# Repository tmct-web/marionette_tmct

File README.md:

# marionette_tmct

## What is "Marionette" ?
Marionettes are so-called puppets.We created this to remotely control multiple remote devices via USB from a single PC.

This system contains two Arduino Leonardo, the controlling side (master side) and the controlled side (slave side).

For example, the USB port connected to the controlling side (master side) is USB-COM, and the USB port connected to the controlled side (slave side) is an HID keyboard (= the slave side looks like a normal HID keyboard). Then you can control the slave keyboard with USB-COM on the master.

マリオネッテと書いてマリオネットと読みます。マリオネットはいわゆる操り人形のことですね。
もともと1台のパソコンからUSB経由で複数の相手機器を遠隔コントロールするために作ったものです。

このシステムは、制御する側（マスタ側）・制御される側（スレーブ側）の2つ分のArduino Leonardoが入っている、ちょっと変わったハードウェアになっています。

たとえば制御する側（マスタ側）に繋がるUSBポートはUSB-COM、制御される側（スレーブ側）につながるUSBポートはHIDキーボード（＝スレーブ側は普通のHIDキーボードに見える）、という構成にすると、マスタ側のUSB-COMでスレーブ側をキーボード制御する、なんてことができます。

## Hardware specifications
Marionette has two circuits of Arduino Leonardo.

The two circuits are called a master (MASTER) and a slave (SLAVE), respectively, and can be operated completely differently by different programs. The hardware block diagram is shown below.

MarionetteはArduino Leonardoの2枚分の回路が実装されています。

2枚分の回路はそれぞれマスタ(MASTER)とスレーブ(SLAVE)と呼び、各々別のプログラムでまったく別の動作をさせることができます。ハードウェアのブロック図を以下に示します。

See our [homepage](https://ss1.xrea.com/tmct.s1009.xrea.com/work/td-ja-7e2g01.html) for more information.(* Japanese only)

詳細は [ホームページ](https://ss1.xrea.com/tmct.s1009.xrea.com/work/td-ja-7e2g01.html) を参照してください。

## Recommended projects
We recommend this project. Compatibility with Marionette is outstanding.

Marionetteで使用すると、良い結果が得られるでしょう。

[NicoHood/HID](https://github.com/NicoHood/HID)

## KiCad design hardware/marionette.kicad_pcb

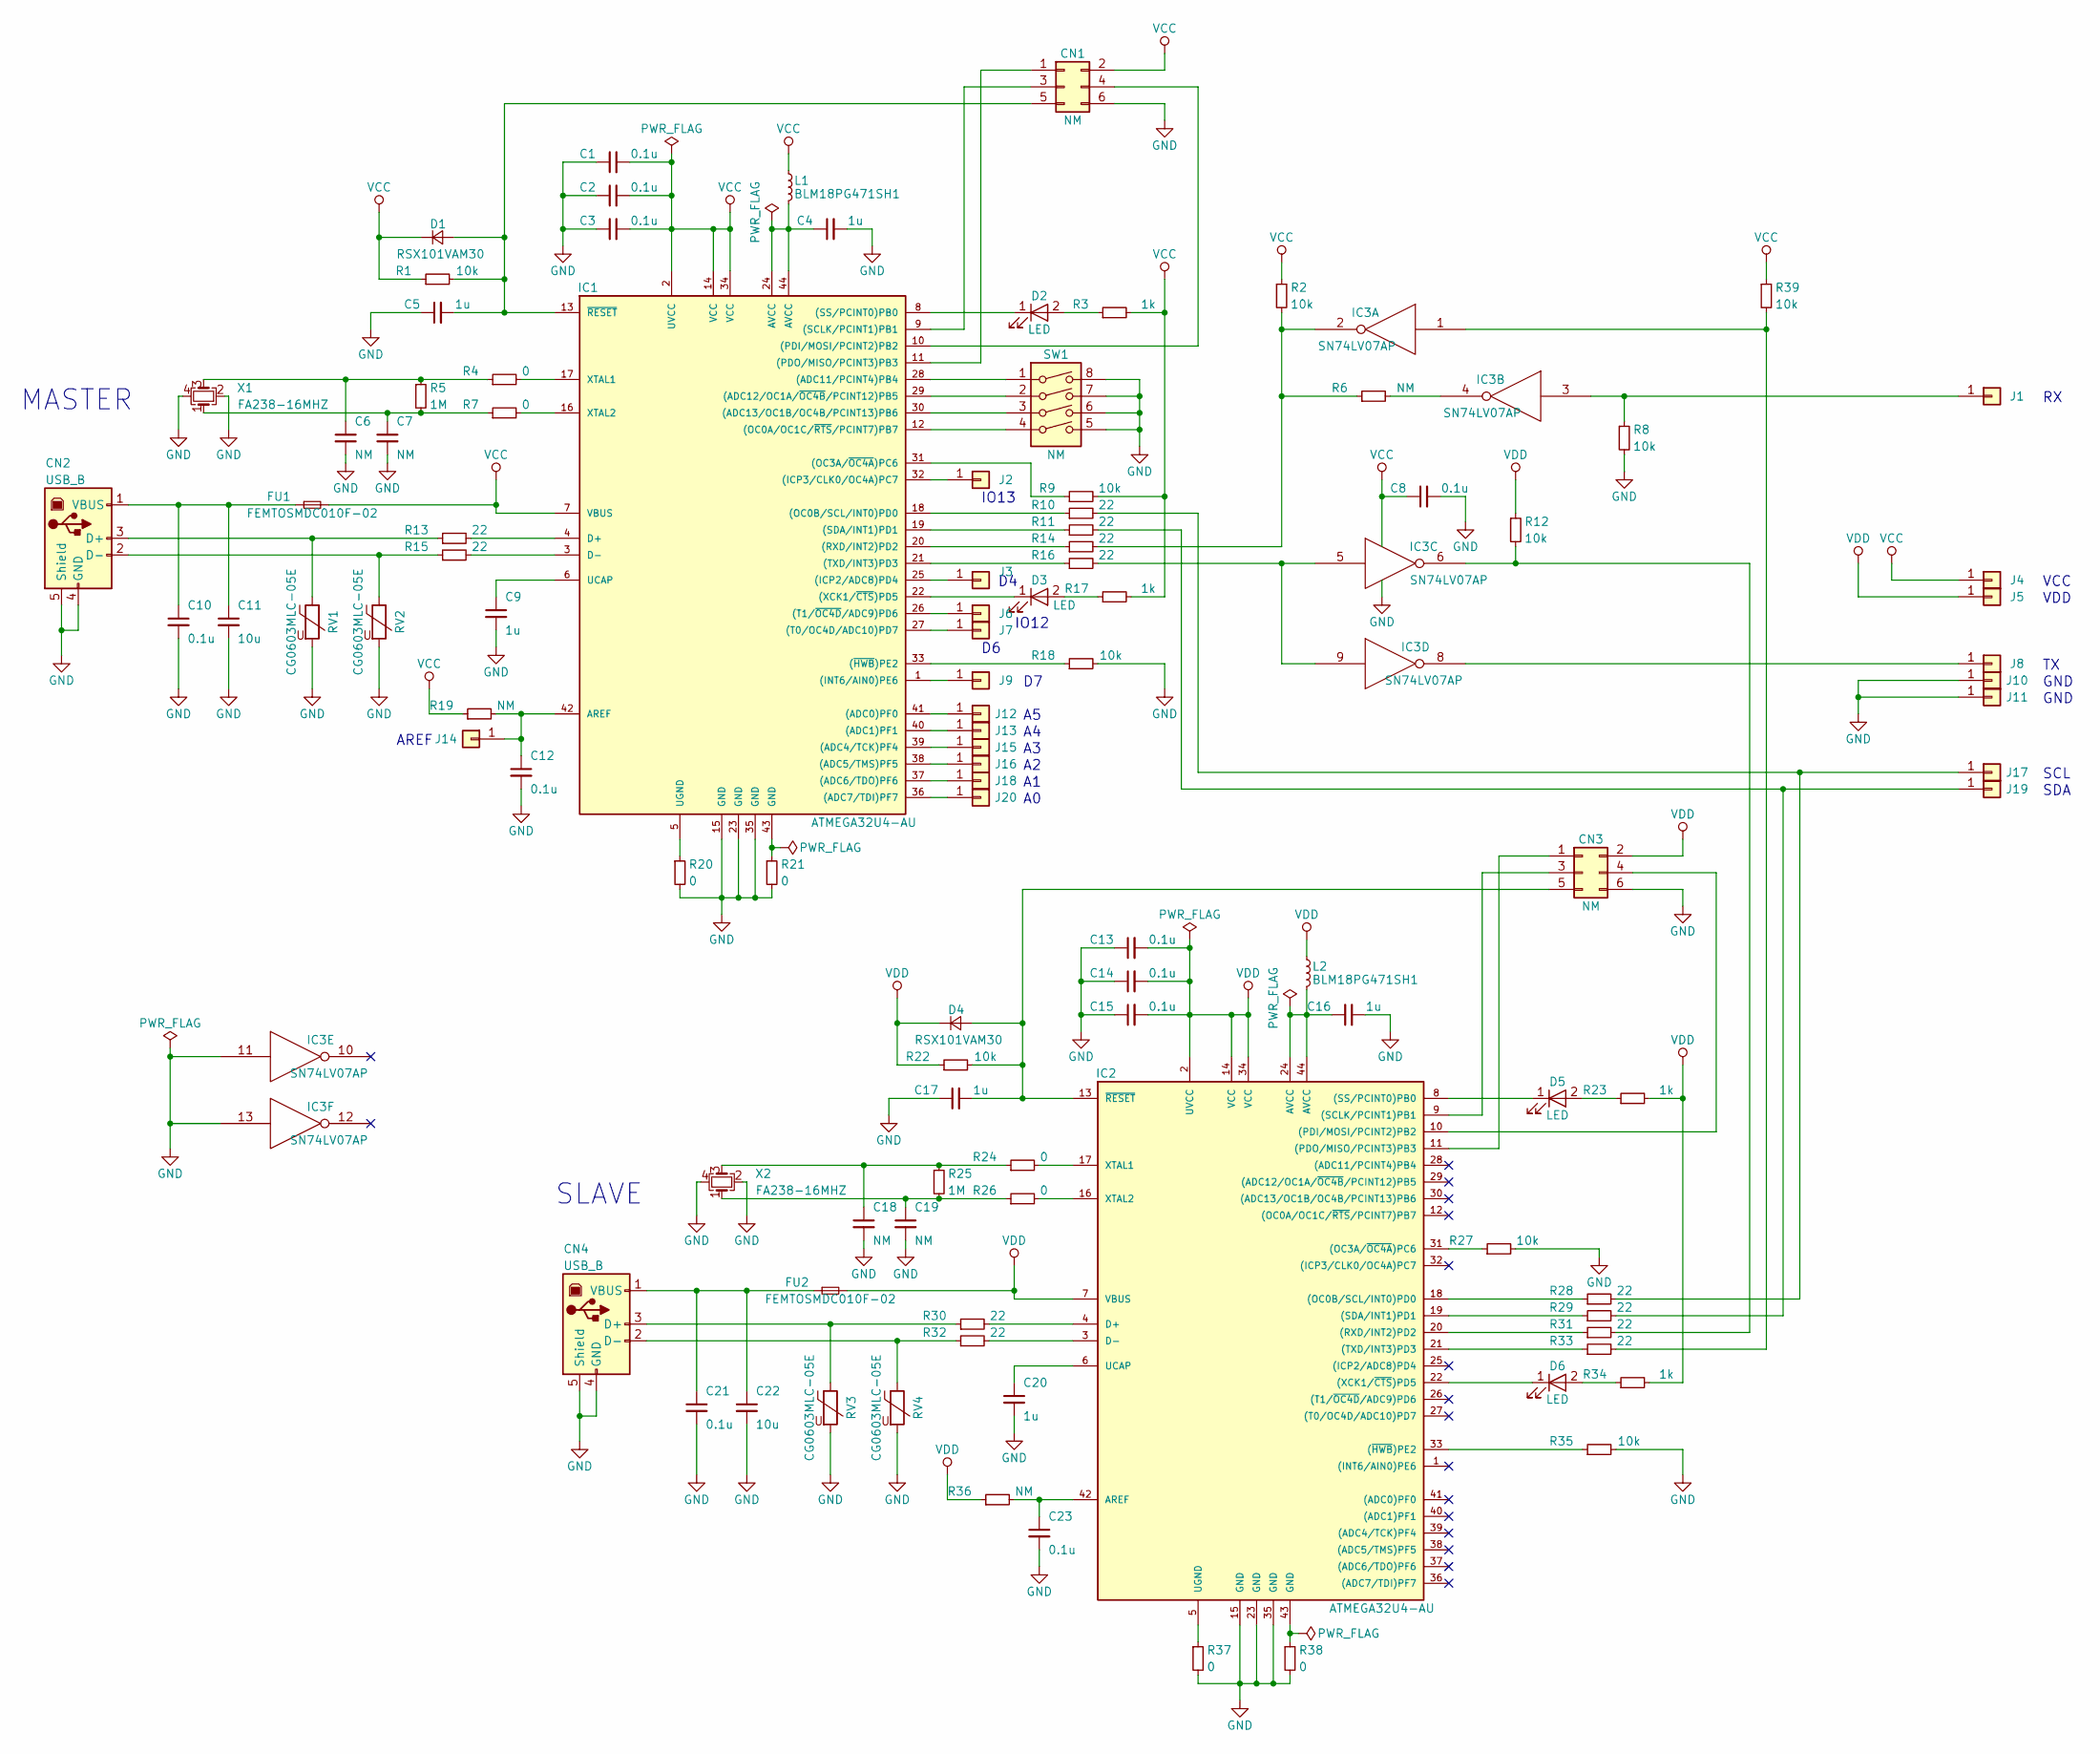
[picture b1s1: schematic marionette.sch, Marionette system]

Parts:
C1, C2, C3, C8, C10, C12, C13, C14, C15, C21, C23: 0.1u; C_0603
C4, C5, C9, C16, C17, C20: 1u; C_0603
C6, C7, C18, C19: NM; C_0603
C11, C22: 10u; C_0805
CN1, CN3: NM; Pin_Header_Straight_2x03_Pitch2.54mm
CN2, CN4: USB_B
D1, D4: RSX101VAM30; D_TUMD2
D2, D3, D5, D6: LED; LED_0603
FU1, FU2: FEMTOSMDC010F-02; C_0603
IC1, IC2: ATMEGA32U4-AU; TQFP-44_10x10mm_Pitch0.8mm
IC3: SN74LV07AP; TSSOP-14_4.4x5mm_Pitch0.65mm
J1, J2, J3, J4, J5, J6, J7, J8, J9, J10, J11, J12, J13, J14, J15, J16, J17, J18, J19, J20: Conn_01x01; Measurement_Point_Round-TH_Small
L1, L2: BLM18PG471SH1; L_0603
R1, R2, R8, R9, R12, R18, R22, R27, R35, R39: 10k; R_0603
R3, R17, R23, R34: 1k; R_0603
R4, R7, R20, R21, R24, R26, R37, R38: 0; R_0603
R5, R25: 1M; R_0603
R6, R19, R36: NM; R_0603
R10, R11, R13, R14, R15, R16, R28, R29, R30, R31, R32, R33: 22; R_0603
RV1, RV2, RV3, RV4: CG0603MLC-05E; C_0603
SW1: NM; DIP-8_W7.62mm_LongPads
X1, X2: FA238-16MHZ; Crystal_SMD_3225-4pin_3.2x2.5mm

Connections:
GND: C1.1, C2.1, C3.1, C4.2, C5.1, C6.2, C7.2, C8.2, C9.2, C10.2, C11.2, C12.2, C13.1, C14.1, C15.1, C16.2, C17.1, C18.2, C19.2, C20.2, C21.2, C22.2, C23.2, CN1.6, CN2.4 (GND), CN2.5 (Shield), CN3.6, CN4.4 (GND), CN4.5 (Shield), IC1.15 (GND), IC1.23 (GND), IC1.35 (GND), IC2.15 (GND), IC2.23 (GND), IC2.35 (GND), IC3.7 (GND), IC3.11, IC3.13, J10.1, J11.1, R8.2, R18.2, R20.2, R21.2, R27.2, R35.2, R37.2, R38.2, RV1.2, RV2.2, RV3.2, RV4.2, SW1.5, SW1.6, SW1.7, SW1.8, X1.2, X1.4, X2.2, X2.4
unnamed: C4.1, IC1.24 (AVCC), IC1.44 (AVCC), L1.2
unnamed: C5.2, CN1.5, D1.2 (A), IC1.13 (~RESET~), R1.2
unnamed: C6.1, R4.1, R5.1, X1.3
unnamed: C7.1, R5.2, R7.1, X1.1
unnamed: C9.1, IC1.6 (UCAP)
unnamed: C10.1, C11.1, CN2.1 (VBUS), FU1.1
unnamed: C12.1, IC1.42 (AREF), J14.1, R19.2
unnamed: C16.1, IC2.24 (AVCC), IC2.44 (AVCC), L2.2
unnamed: C17.2, CN3.5, D4.2 (A), IC2.13 (~RESET~), R22.2
unnamed: C18.1, R24.1, R25.1, X2.3
unnamed: C19.1, R25.2, R26.1, X2.1
unnamed: C20.1, IC2.6 (UCAP)
unnamed: C21.1, C22.1, CN4.1 (VBUS), FU2.1
unnamed: C23.1, IC2.42 (AREF), R36.2
unnamed: CN1.1, IC1.11 ((PDO/MISO/PCINT3)PB3)
unnamed: CN1.3, IC1.9 ((SCLK/PCINT1)PB1)
unnamed: CN1.4, IC1.10 ((PDI/MOSI/PCINT2)PB2)
unnamed: CN2.2 (D-), R15.1, RV2.1
unnamed: CN2.3 (D+), R13.1, RV1.1
unnamed: CN3.1, IC2.11 ((PDO/MISO/PCINT3)PB3)
unnamed: CN3.3, IC2.9 ((SCLK/PCINT1)PB1)
unnamed: CN3.4, IC2.10 ((PDI/MOSI/PCINT2)PB2)
unnamed: CN4.2 (D-), R32.1, RV4.1
unnamed: CN4.3 (D+), R30.1, RV3.1
unnamed: D2.1 (K), IC1.8 ((SS/PCINT0)PB0)
unnamed: D2.2 (A), R3.1
unnamed: D3.1 (K), IC1.22 ((XCK1/~CTS~)PD5)
unnamed: D3.2 (A), R17.1
unnamed: D5.1 (K), IC2.8 ((SS/PCINT0)PB0)
unnamed: D5.2 (A), R23.1
unnamed: D6.1 (K), IC2.22 ((XCK1/~CTS~)PD5)
unnamed: D6.2 (A), R34.1
unnamed: IC1.1 ((INT6/AIN0)PE6), J9.1
unnamed: IC1.3 (D-), R15.2
unnamed: IC1.4 (D+), R13.2
unnamed: IC1.5 (UGND), R20.1
unnamed: IC1.12 ((OC0A/OC1C/~RTS~/PCINT7)PB7), SW1.4
unnamed: IC1.16 (XTAL2), R7.2
unnamed: IC1.17 (XTAL1), R4.2
unnamed: IC1.18 ((OC0B/SCL/INT0)PD0), R10.1
unnamed: IC1.19 ((SDA/INT1)PD1), R11.1
unnamed: IC1.20 ((RXD/INT2)PD2), R14.1
unnamed: IC1.21 ((TXD/INT3)PD3), R16.1
unnamed: IC1.25 ((ICP2/ADC8)PD4), J3.1
unnamed: IC1.26 ((T1/~OC4D~/ADC9)PD6), J6.1
unnamed: IC1.27 ((T0/OC4D/ADC10)PD7), J7.1
unnamed: IC1.28 ((ADC11/PCINT4)PB4), SW1.1
unnamed: IC1.29 ((ADC12/OC1A/~OC4B~/PCINT12)PB5), SW1.2
unnamed: IC1.30 ((ADC13/OC1B/OC4B/PCINT13)PB6), SW1.3
unnamed: IC1.31 ((OC3A/~OC4A~)PC6), R9.1
unnamed: IC1.32 ((ICP3/CLK0/OC4A)PC7), J2.1
unnamed: IC1.33 ((~HWB~)PE2), R18.1
unnamed: IC1.36 ((ADC7/TDI)PF7), J20.1
unnamed: IC1.37 ((ADC6/TDO)PF6), J18.1
unnamed: IC1.38 ((ADC5/TMS)PF5), J16.1
unnamed: IC1.39 ((ADC4/TCK)PF4), J15.1
unnamed: IC1.40 ((ADC1)PF1), J13.1
unnamed: IC1.41 ((ADC0)PF0), J12.1
unnamed: IC1.43 (GND), R21.1
unnamed: IC2.3 (D-), R32.2
unnamed: IC2.4 (D+), R30.2
unnamed: IC2.5 (UGND), R37.1
unnamed: IC2.16 (XTAL2), R26.2
unnamed: IC2.17 (XTAL1), R24.2
unnamed: IC2.18 ((OC0B/SCL/INT0)PD0), R28.1
unnamed: IC2.19 ((SDA/INT1)PD1), R29.1
unnamed: IC2.20 ((RXD/INT2)PD2), R31.1
unnamed: IC2.21 ((TXD/INT3)PD3), R33.1
unnamed: IC2.31 ((OC3A/~OC4A~)PC6), R27.1
unnamed: IC2.33 ((~HWB~)PE2), R35.1
unnamed: IC2.43 (GND), R38.1
unnamed: IC3.1, R33.2, R39.2
unnamed: IC3.2, R2.2, R6.1, R14.2
unnamed: IC3.3, J1.1, R8.1
unnamed: IC3.4, R6.2
unnamed: IC3.5, IC3.9, R16.2
unnamed: IC3.6, R12.2, R31.2
unnamed: IC3.8, J8.1
unnamed: J17.1, R10.2, R28.2
unnamed: J19.1, R11.2, R29.2
VCC: C1.2, C2.2, C3.2, C8.1, CN1.2, D1.1 (K), FU1.2, IC1.2 (UVCC), IC1.7 (VBUS), IC1.14 (VCC), IC1.34 (VCC), IC3.14 (VCC), J4.1, L1.1, R1.1, R2.1, R3.2, R9.2, R17.2, R19.1, R39.1
VDD: C13.2, C14.2, C15.2, CN3.2, D4.1 (K), FU2.2, IC2.2 (UVCC), IC2.7 (VBUS), IC2.14 (VCC), IC2.34 (VCC), J5.1, L2.1, R12.1, R22.1, R23.2, R34.2, R36.1

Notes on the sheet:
MASTER
SLAVE
AREF
VCC
VDD
GND
SCL
SDA
IO13
IO12

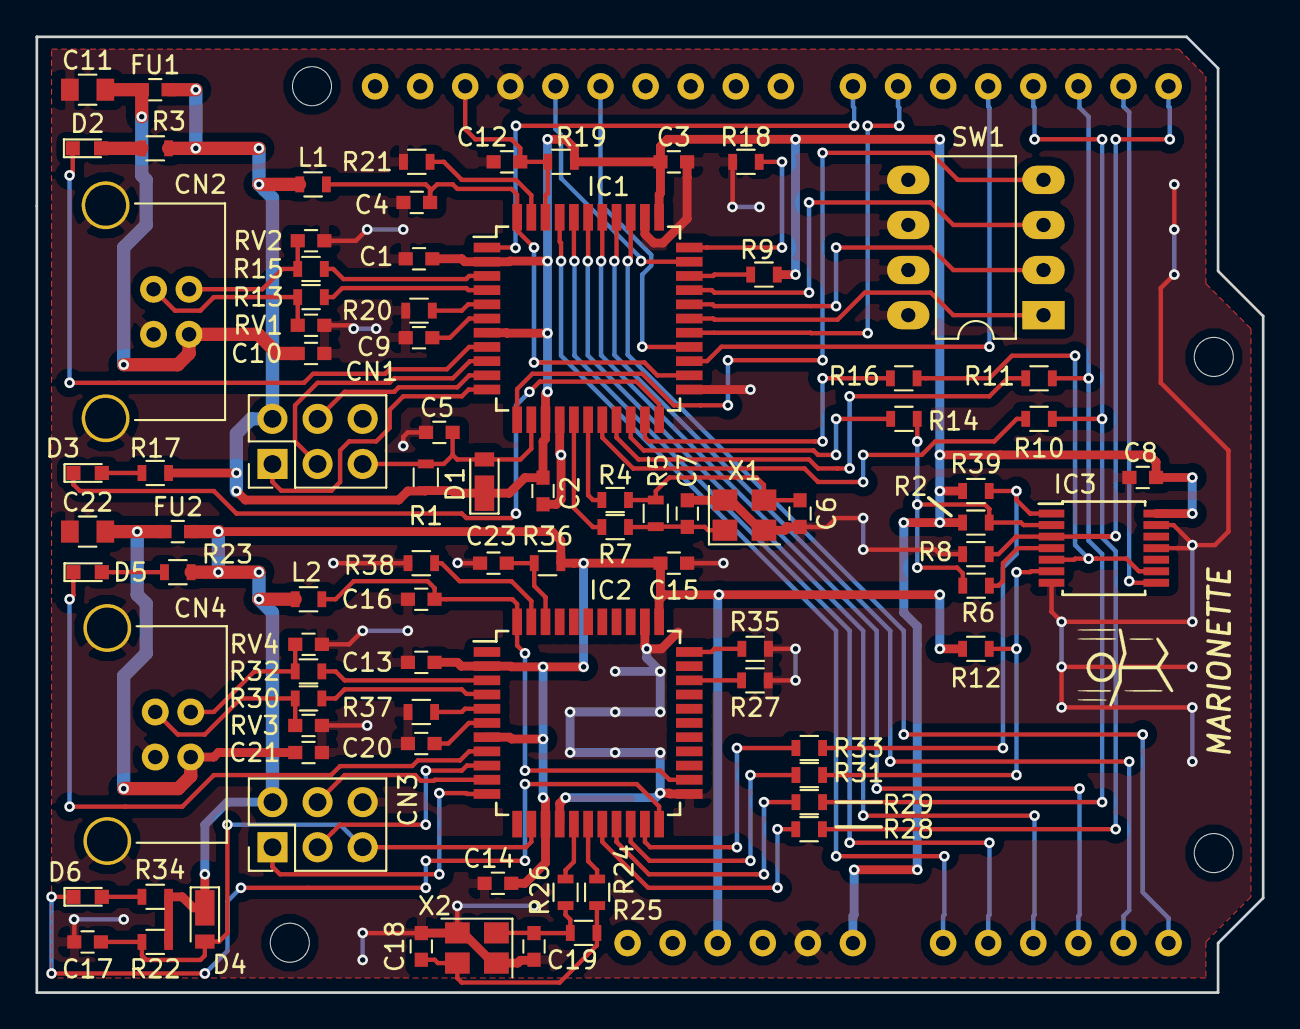
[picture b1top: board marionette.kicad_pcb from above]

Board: 2 copper layers, 69.1 x 53.8 mm, 110 parts (0 on the bottom side), 83 nets.

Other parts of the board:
REF100, REF101, REF102, REF103: MountingHole_2.2mm_M2

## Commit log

2020-01-04 Initial release
    Initial release
2022-02-05 Update README.md
    Fixed a broken link in 'readme.md'
